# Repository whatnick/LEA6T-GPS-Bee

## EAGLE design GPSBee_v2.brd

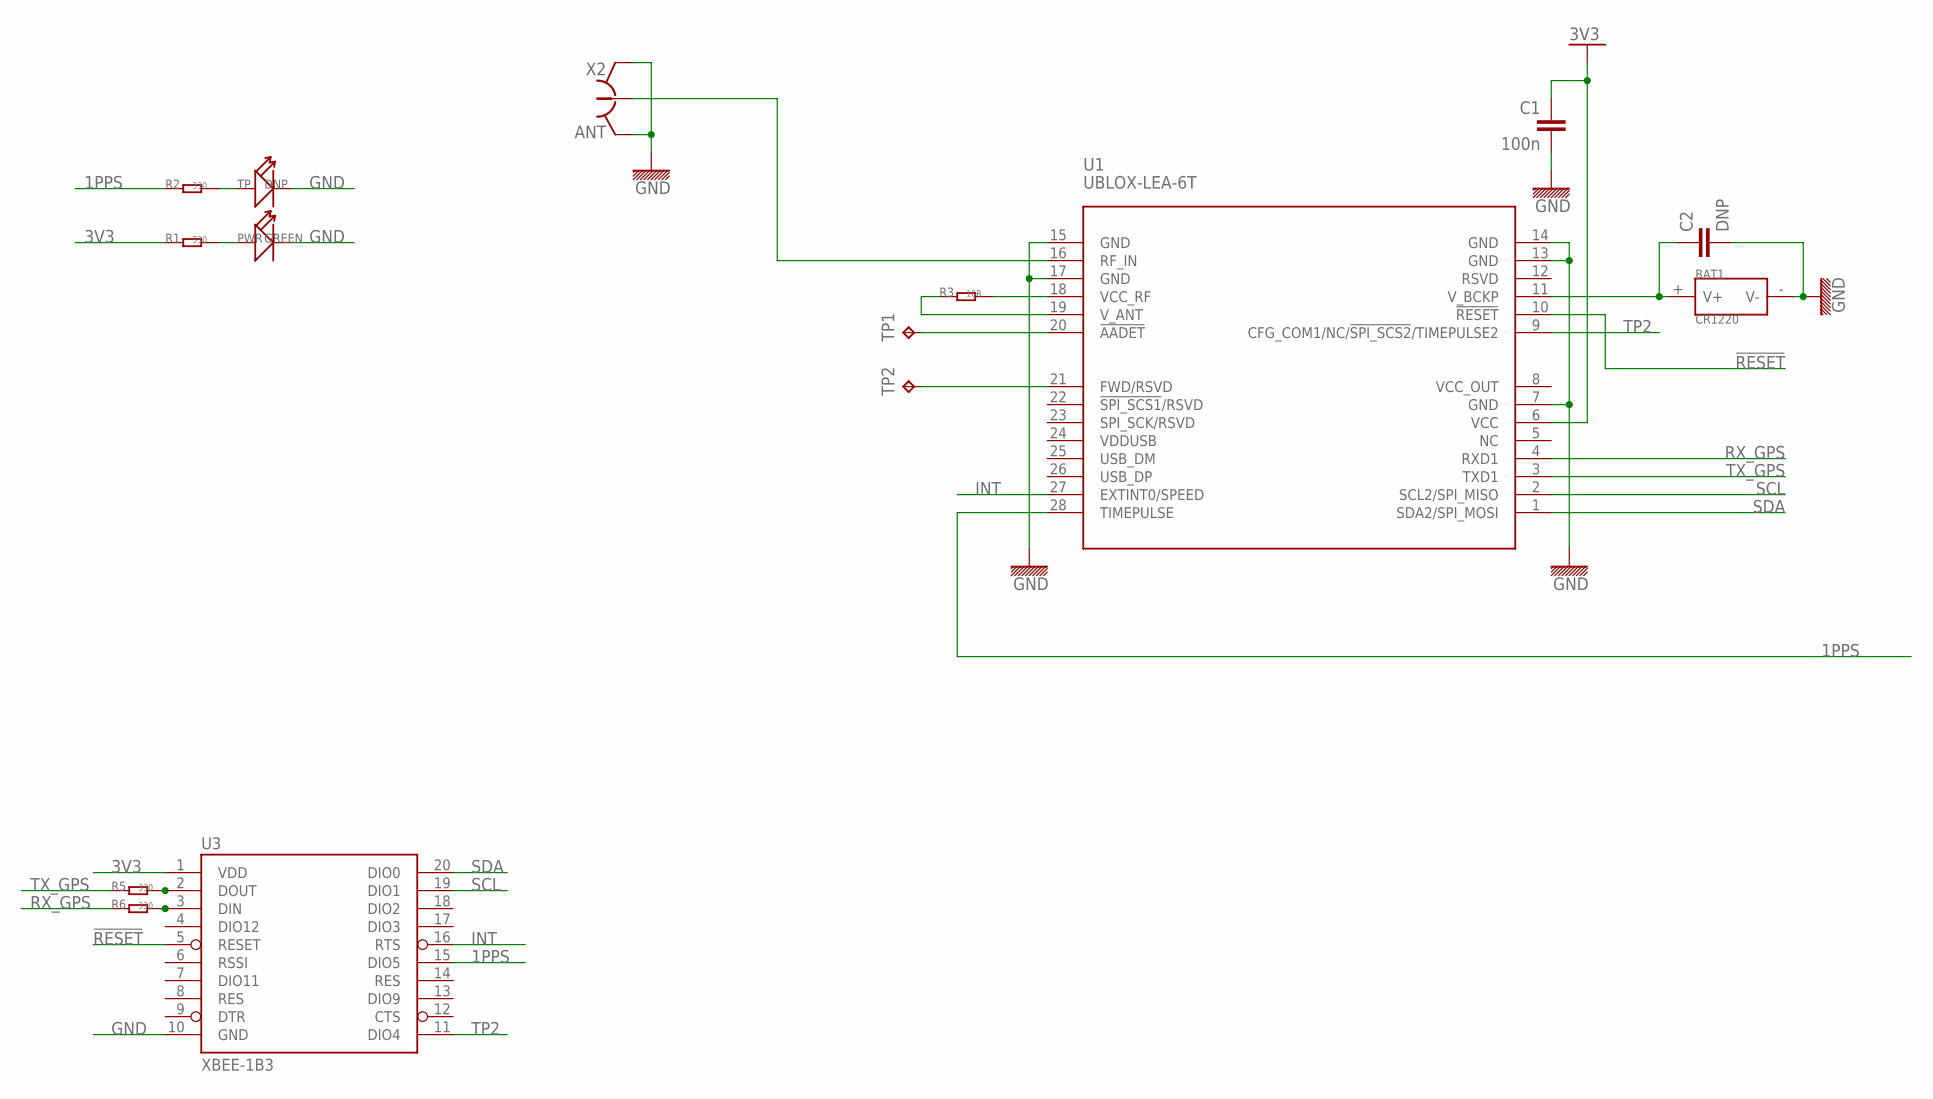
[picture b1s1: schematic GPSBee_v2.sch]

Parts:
BAT1: CR1220; PLASTIC-CR1220-L15.06XW13.0XH4.1MM
C1: 100n; 0603
C2: DNP; 0603
PWR: GREEN; LED-0603
R1, R2, R5, R6: 330; 0603
R3: 10R; 0603
TP: DNP; LED-0603
TP1, TP2: TPTP10R; TP10R
U1: UBLOX-LEA-6T; UBLOX-LEA-6
U3: XBEE-1B3; XBEE-SMD
X2: ANT; HRS_UFL

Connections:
1PPS: R2.1, U1.28 (TIMEPULSE), U3.15 (DIO5)
3V3: C1.1, R1.1, U1.6 (VCC), U3.1 (VDD)
!RESET: U1.10 (!RESET), U3.5 (RESET)
GND: BAT1.- (V-), C1.2, C2.2, PWR.-, TP.-, U1.7 (GND), U1.13 (GND), U1.14 (GND), U1.15 (GND), U1.17 (GND), U3.10 (GND), X2.GND@1 (GND), X2.GND@2 (GND)
INT: U1.27 (EXTINT0/SPEED), U3.16 (RTS)
unnamed: PWR.+, R1.2
unnamed: R6.2, U3.3 (DIN)
unnamed: TP1.TP, U1.20 (!AADET)
unnamed: R5.2, U3.2 (DOUT)
unnamed: R2.2, TP.+
unnamed: TP2.TP, U1.21 (FWD/RSVD)
unnamed: R3.2, U1.18 (VCC_RF)
unnamed: R3.1, U1.19 (V_ANT)
unnamed: BAT1.+ (V+), C2.1, U1.11 (V_BCKP)
unnamed: U1.16 (RF_IN), X2.SIG (1)
RX_GPS: R6.1, U1.4 (RXD1)
SCL: U1.2 (SCL2/SPI_MISO), U3.19 (DIO1)
SDA: U1.1 (SDA2/SPI_MOSI), U3.20 (DIO0)
TP2: U1.9 (CFG_COM1/NC/!SPI_SCS2!/TIMEPULSE2), U3.11 (DIO4)
TX_GPS: R5.1, U1.3 (TXD1)
VCC_OUT: U1.8 (VCC_OUT)
VDDUSB: U1.24 (VDDUSB)

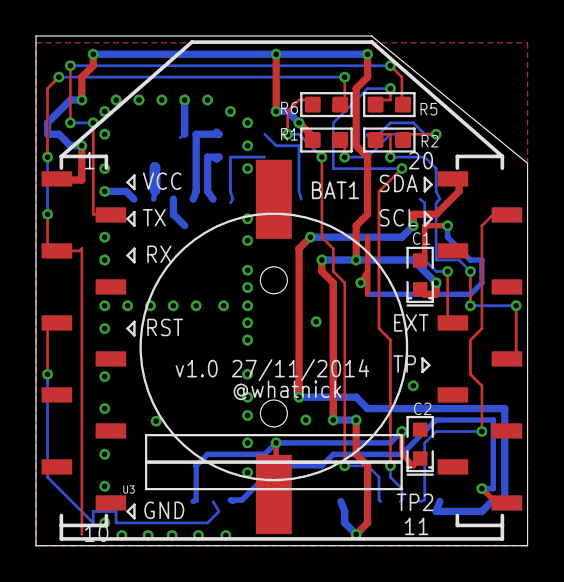
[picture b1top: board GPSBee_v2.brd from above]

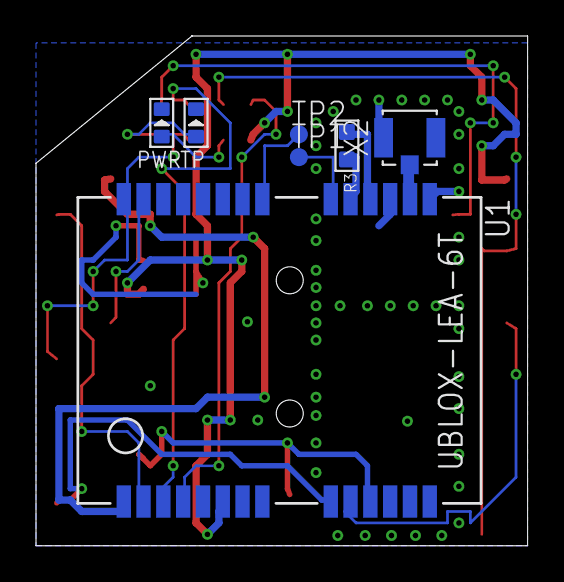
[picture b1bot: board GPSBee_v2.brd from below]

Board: 2 copper layers, 27.3 x 28.3 mm, 15 parts (7 on the bottom side), 20 nets.

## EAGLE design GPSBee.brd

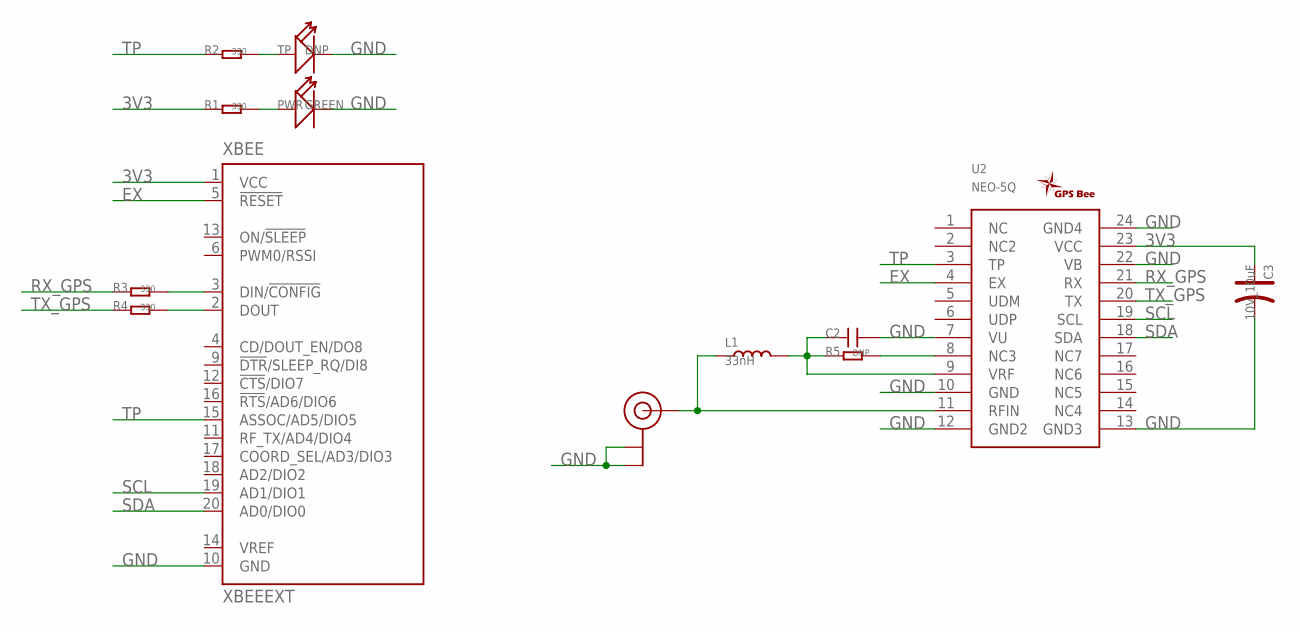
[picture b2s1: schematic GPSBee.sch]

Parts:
C2: C-0603; 0603
C3: 10V_10uF; AVX-A
L1: 33nH; 0603
LOGO1: GPSLOGO_SLIK; GPSLOGO
PWR: GREEN; LED-0603
R1, R2, R3, R4: 330; 0603
R5: DNP; 0603
TP: DNP; LED-0603
U2: NEO-5Q
U3: U.FL
XBEE: XBEEEXT; XBEE_PLUG

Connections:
3V3: C3.+, R1.1, U2.23 (VCC), XBEE.1 (VCC)
EX: U2.4 (EX), XBEE.5 (!RESET)
GND: C2.2, C3.-, PWR.-, TP.-, U2.7 (VU), U2.10 (GND), U2.12 (GND2), U2.13 (GND3), U2.22 (VB), U2.24 (GND4), U3.P$1 (GND), U3.P$2 (GND), XBEE.10 (GND)
unnamed: PWR.+, R1.2
unnamed: L1.1, U2.11 (RFIN), U3.P$3 (SIGNAL)
unnamed: C2.1, L1.2, R5.1, U2.9 (VRF)
unnamed: R3.2, XBEE.3 (DIN/!CONFIG)
unnamed: R2.2, TP.+
unnamed: R4.2, XBEE.2 (DOUT)
unnamed: R5.2, U2.8 (NC3)
RX_GPS: R3.1, U2.21 (RX)
SCL: U2.19 (SCL), XBEE.19 (AD1/DIO1)
SDA: U2.18 (SDA), XBEE.20 (AD0/DIO0)
TP: R2.1, U2.3 (TP), XBEE.15 (ASSOC/AD5/DIO5)
TX_GPS: R4.1, U2.20 (TX)

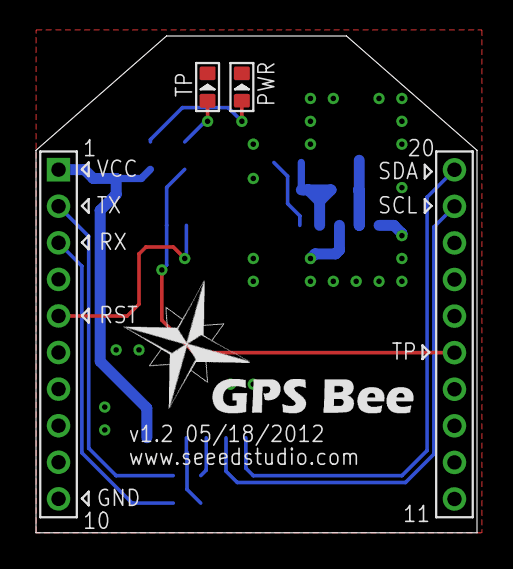
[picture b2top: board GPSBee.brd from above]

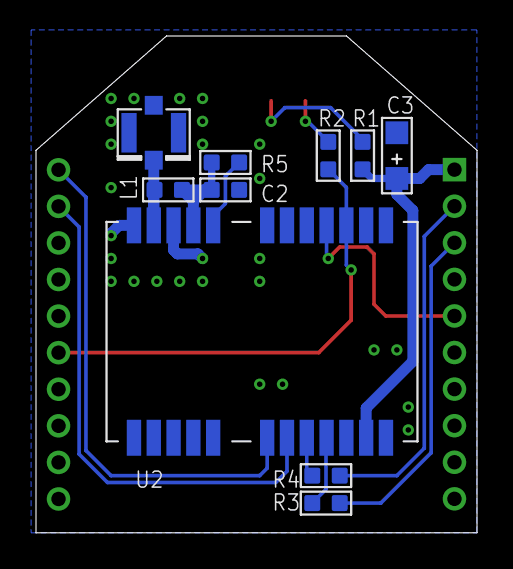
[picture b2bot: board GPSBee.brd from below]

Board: 2 copper layers, 24.5 x 27.6 mm, 14 parts (10 on the bottom side), 15 nets.

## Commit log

2014-11-18 Initial import of design parts
2014-11-27 Pulled in design from osmo-lea-6T board
2014-11-27 Widened power trace
2014-11-28 Changed DRU and added new frame

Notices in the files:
parts and their libraries:
SparkFun-RF: Licensing: Creative Commons ShareAlike 4.0 International - https://creativecommons.org/licenses/by-sa/4.0
